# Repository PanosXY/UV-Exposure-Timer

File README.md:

UV-Exposure-Timer
=================

Timer for UV Exposure box

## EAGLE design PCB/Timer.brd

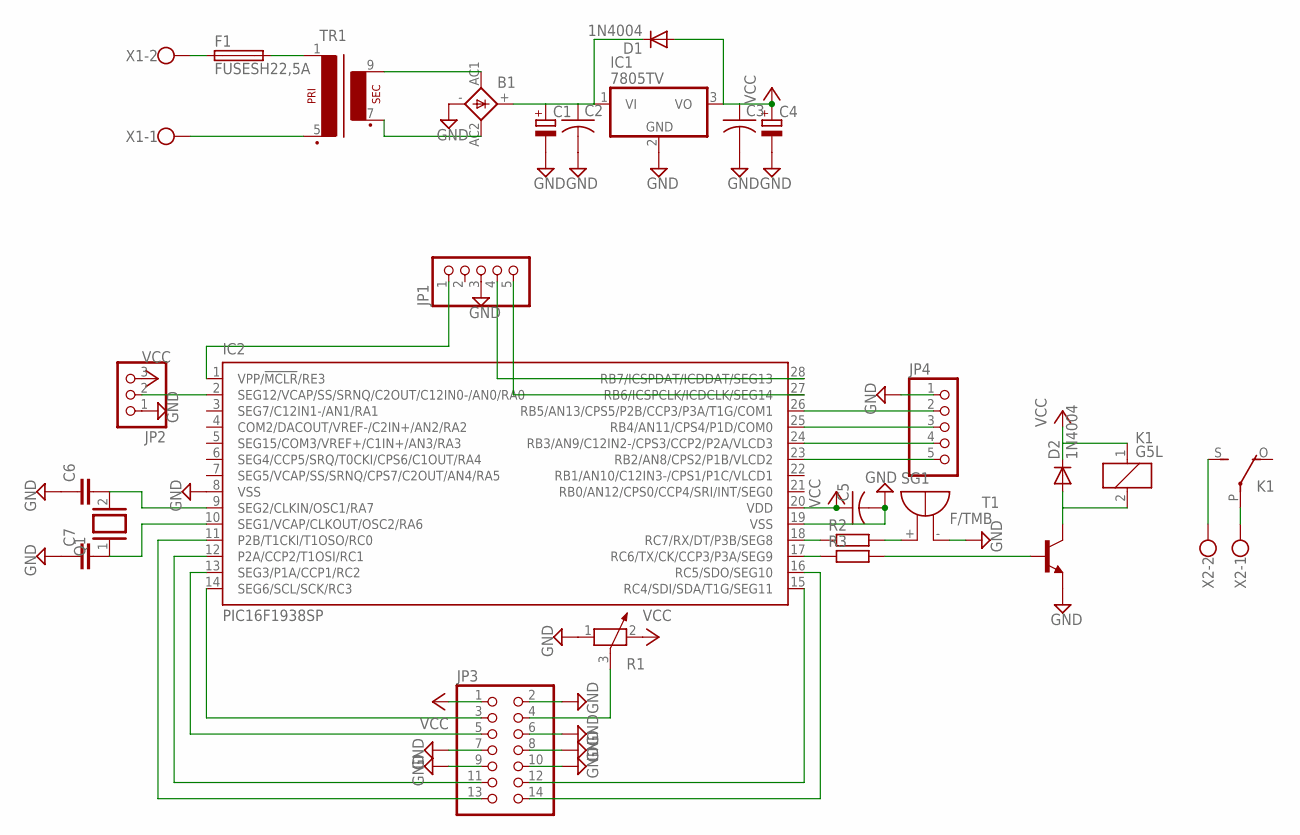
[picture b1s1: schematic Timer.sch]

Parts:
B1: 1KAB
C1: CPOL-EUE5-13; E5-13
C2, C3, C5: C-US050-030X075; C050-030X075
C4: CPOL-EUE3.5-8; E3,5-8
C6, C7: C2,5-3; C2.5-3
D1, D2: 1N4004; DO41-10
F1: FUSESH22,5A; SH22,5A
IC1: 7805TV; TO220V
IC2: PIC16F1938SP; DIL28-3
JP1, JP4: PINHD-1X5; 1X05
JP2: PINHD-1X3; 1X03
JP3: PINHD-2X7; 2X07
K1: G5L; G5LE
Q1: XTAL/S; QS
R1: POTENTIOMETER_PT-10; PT-10
R2, R3: R-EU_0207/10; 0207/10
SG1: F/TMB
T1: BC547-NPN-TO92-CBE; TO92-CBE
TR1: VV11
X1, X2: W237-102

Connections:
GND: B1.-, C1.-, C2.2, C3.2, C4.-, C5.2, C6.1, C7.1, IC1.2 (GND), IC2.8 (VSS), IC2.19 (VSS), JP1.3, JP2.1, JP3.2, JP3.6, JP3.7, JP3.8, JP3.9, JP3.10, JP4.1, R1.1, SG1.-, T1.E
unnamed: JP3.4, R1.3
unnamed: F1.1, X1.2
unnamed: F1.2, TR1.1
unnamed: TR1.5 (P2), X1.1
unnamed: B1.AC1, TR1.9 (S4)
unnamed: B1.AC2, TR1.7 (S3)
unnamed: B1.+, C1.+, C2.1, D1.C, IC1.1 (VI)
unnamed: IC2.1 (VPP/!MCLR!/RE3), JP1.1
unnamed: IC2.28 (RB7/ICSPDAT/ICDDAT/SEG13), JP1.4
unnamed: IC2.27 (RB6/ICSPCLK/ICDCLK/SEG14), JP1.5
unnamed: IC2.2 (SEG12/VCAP/SS/SRNQ/C2OUT/C12IN0-/AN0/RA0), JP2.2
unnamed: IC2.14 (SEG6/SCL/SCK/RC3), JP3.3
unnamed: C6.2, IC2.9 (SEG2/CLKIN/OSC1/RA7), Q1.2
unnamed: C7.2, IC2.10 (SEG1/VCAP/CLKOUT/OSC2/RA6), Q1.1
unnamed: IC2.13 (SEG3/P1A/CCP1/RC2), JP3.5
unnamed: IC2.12 (P2A/CCP2/T1OSI/RC1), JP3.11
unnamed: IC2.11 (P2B/T1CKI/T1OSO/RC0), JP3.13
unnamed: IC2.15 (RC4/SDI/SDA/T1G/SEG11), JP3.12
unnamed: IC2.16 (RC5/SDO/SEG10), JP3.14
unnamed: IC2.26 (RB5/AN13/CPS5/P2B/CCP3/P3A/T1G/COM1), JP4.2
unnamed: IC2.25 (RB4/AN11/CPS4/P1D/COM0), JP4.3
unnamed: IC2.24 (RB3/AN9/C12IN2-/CPS3/CCP2/P2A/VLCD3), JP4.4
unnamed: IC2.23 (RB2/AN8/CPS2/P1B/VLCD2), JP4.5
unnamed: IC2.18 (RC7/RX/DT/P3B/SEG8), R2.1
unnamed: R2.2, SG1.+
unnamed: IC2.17 (RC6/TX/CK/CCP3/P3A/SEG9), R3.1
unnamed: R3.2, T1.B
unnamed: D2.A, K1.2, T1.C
unnamed: K1.P, X2.1
unnamed: K1.S, X2.2
VCC: C3.1, C4.+, C5.1, D1.A, D2.C, IC1.3 (VO), IC2.20 (VDD), JP2.3, JP3.1, K1.1, R1.2

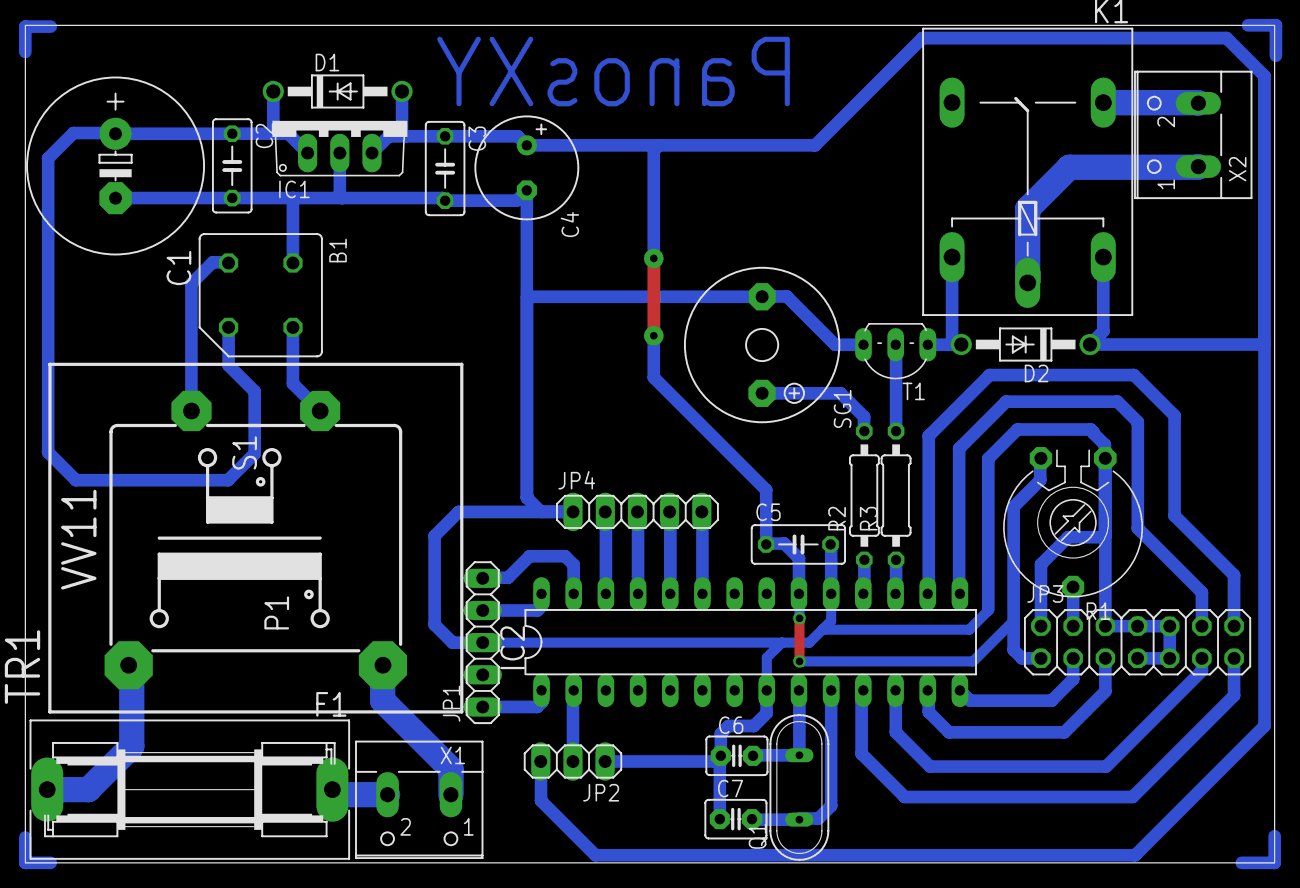
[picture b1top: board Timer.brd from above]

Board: 2 copper layers, 98.6 x 66.1 mm, 27 parts (0 on the bottom side), 32 nets.
